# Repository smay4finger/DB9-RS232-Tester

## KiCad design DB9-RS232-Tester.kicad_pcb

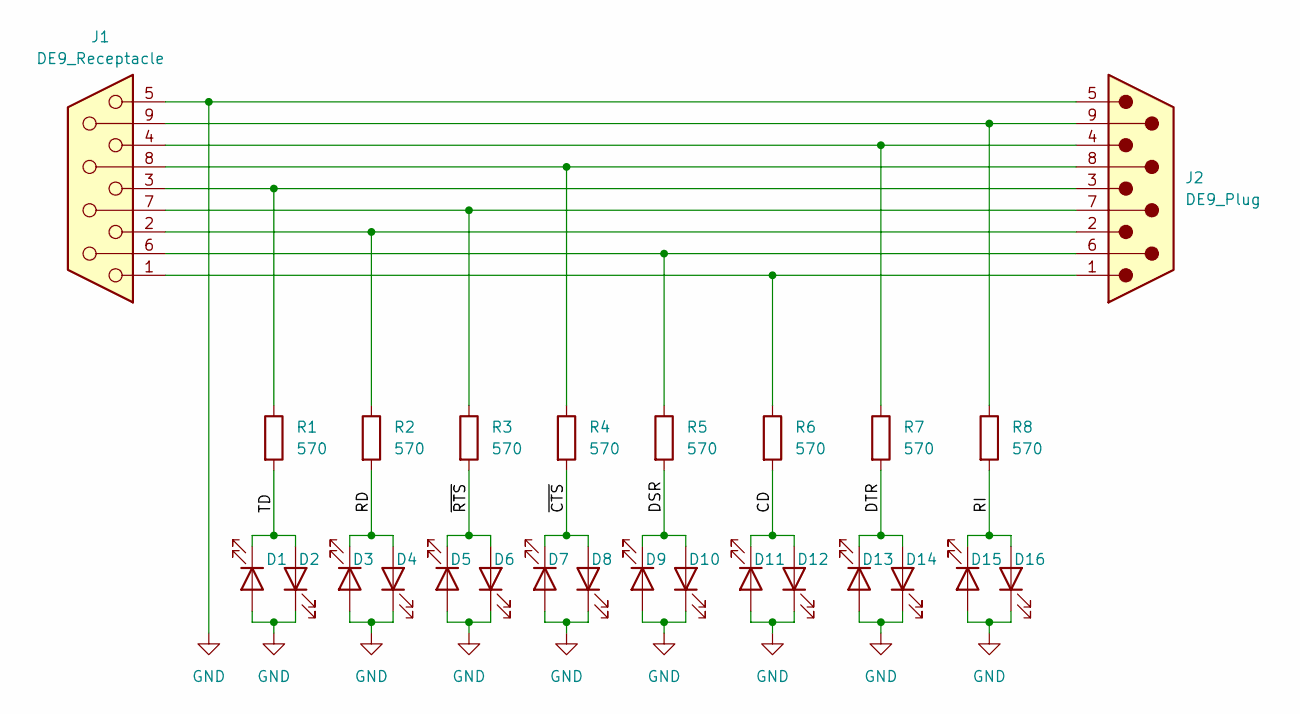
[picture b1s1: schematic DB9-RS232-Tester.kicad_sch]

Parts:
D1, D2, D3, D4, D5, D6, D7, D8, D9, D10, D11, D12, D13, D14, D15, D16: LED; LED_0805_2012Metric_Pad1.15x1.40mm_HandSolder
J1: DE9_Receptacle; DSUB-9_Female_EdgeMount_P2.77mm
J2: DE9_Plug; DSUB-9_Male_EdgeMount_P2.77mm
R1, R2, R3, R4, R5, R6, R7, R8: 570; R_0805_2012Metric_Pad1.20x1.40mm_HandSolder

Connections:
/CD: D11.1 (K), D12.2 (A), R6.2
/DSR: D9.1 (K), D10.2 (A), R5.2
/DTR: D13.1 (K), D14.2 (A), R7.2
/RD: D3.1 (K), D4.2 (A), R2.2
/RI: D15.1 (K), D16.2 (A), R8.2
/TD: D1.1 (K), D2.2 (A), R1.2
/~CTS: D7.1 (K), D8.2 (A), R4.2
/~RTS: D5.1 (K), D6.2 (A), R3.2
GND: D1.2 (A), D2.1 (K), D3.2 (A), D4.1 (K), D5.2 (A), D6.1 (K), D7.2 (A), D8.1 (K), D9.2 (A), D10.1 (K), D11.2 (A), D12.1 (K), D13.2 (A), D14.1 (K), D15.2 (A), D16.1 (K), J1.5, J2.5
unnamed: J1.1, J2.1, R6.1
unnamed: J1.2, J2.2, R2.1
unnamed: J1.3, J2.3, R1.1
unnamed: J1.4, J2.4, R7.1
unnamed: J1.6, J2.6, R5.1
unnamed: J1.7, J2.7, R3.1
unnamed: J1.8, J2.8, R4.1
unnamed: J1.9, J2.9, R8.1

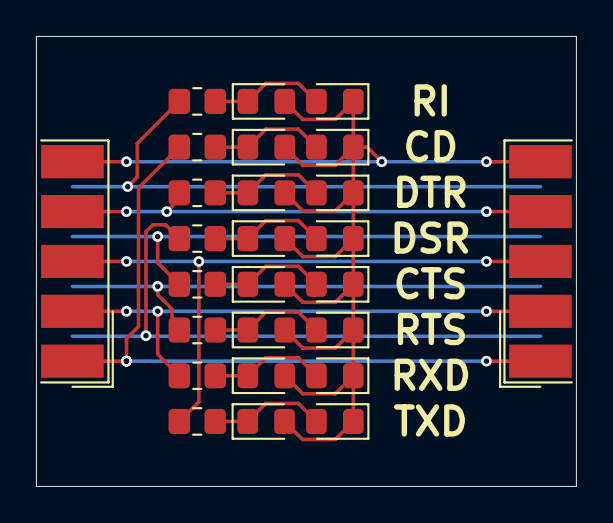
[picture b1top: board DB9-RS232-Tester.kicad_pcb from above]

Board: 4 copper layers, 30.0 x 25.0 mm, 26 parts (0 on the bottom side), 17 nets.
